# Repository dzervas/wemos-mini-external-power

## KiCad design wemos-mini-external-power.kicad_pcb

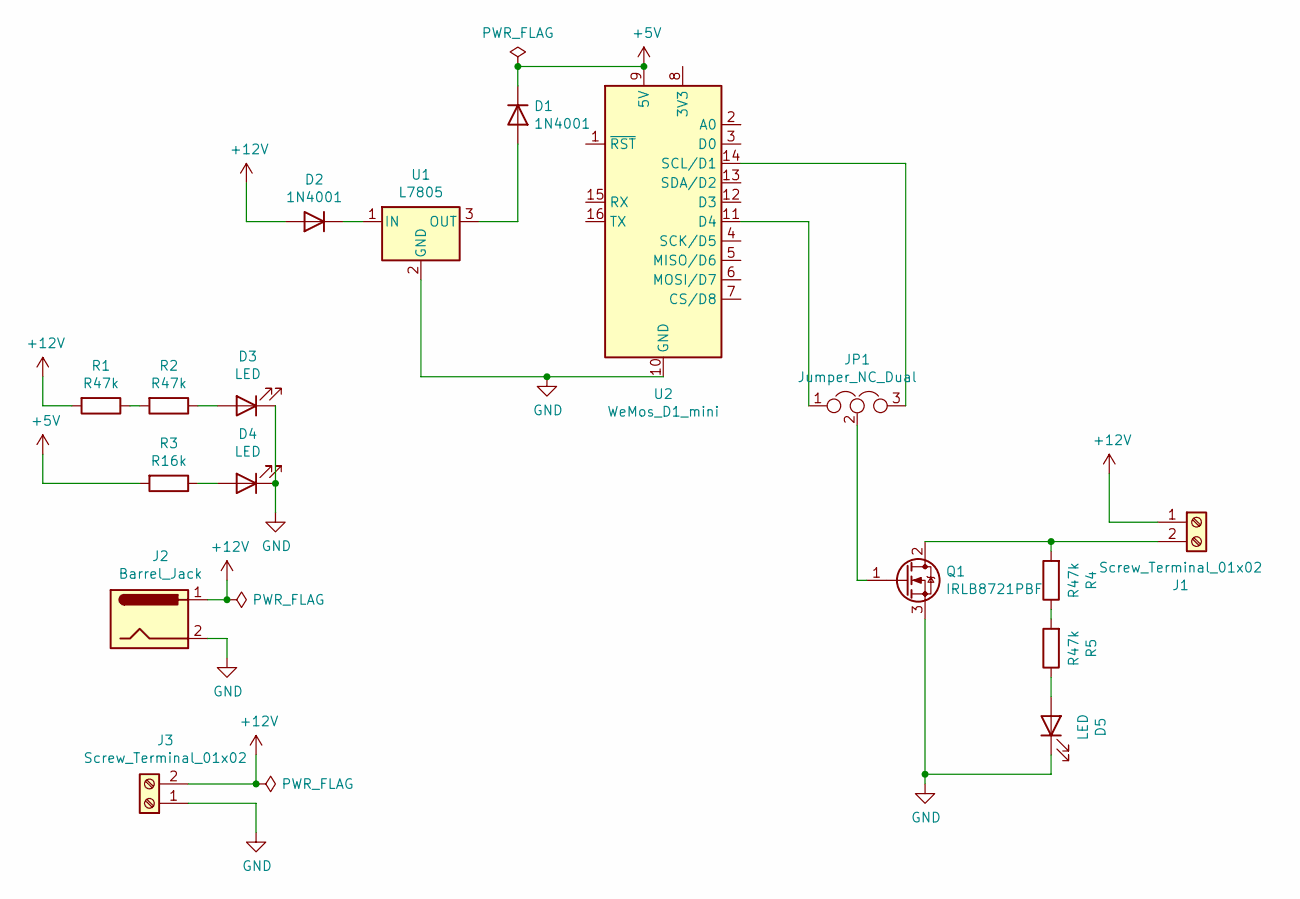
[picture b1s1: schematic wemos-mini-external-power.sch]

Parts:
D1, D2: 1N4001; D_DO-41_SOD81_P7.62mm_Horizontal
D3, D4, D5: LED; LED_1206_3216Metric
J1, J3: Screw_Terminal_01x02; TerminalBlock_4Ucon_1x02_P3.50mm_Horizontal
J2: Barrel_Jack; BarrelJack_CUI_PJ-102AH_Horizontal
JP1: Jumper_NC_Dual; PinHeader_1x03_P2.54mm_Vertical
Q1: IRLB8721PBF; TO-220-3_Vertical
R1, R2, R4, R5: R47k; R_0805_2012Metric
R3: R16k; R_0805_2012Metric
U1: L7805; TO-220-3_Horizontal_TabDown
U2: WeMos_D1_mini; WEMOS_D1_mini_light

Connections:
+5V: D1.1 (K), R3.2, U2.9 (5V)
+12V: D2.2 (A), J1.1, J2.1, J3.2, R1.2
GND: D3.1 (K), D4.1 (K), D5.1 (K), J2.2, J3.1, Q1.3 (S), U1.2 (GND), U2.10 (GND)
unnamed: D1.2 (A), U1.3 (OUT)
unnamed: D2.1 (K), U1.1 (IN)
unnamed: D3.2 (A), R2.1
unnamed: D4.2 (A), R3.1
unnamed: D5.2 (A), R5.1
unnamed: J1.2, Q1.2 (D), R4.2
unnamed: JP1.1, U2.11 (D4)
unnamed: JP1.2, Q1.1 (G)
unnamed: JP1.3, U2.14 (SCL/D1)
unnamed: R1.1, R2.2
unnamed: R4.1, R5.2

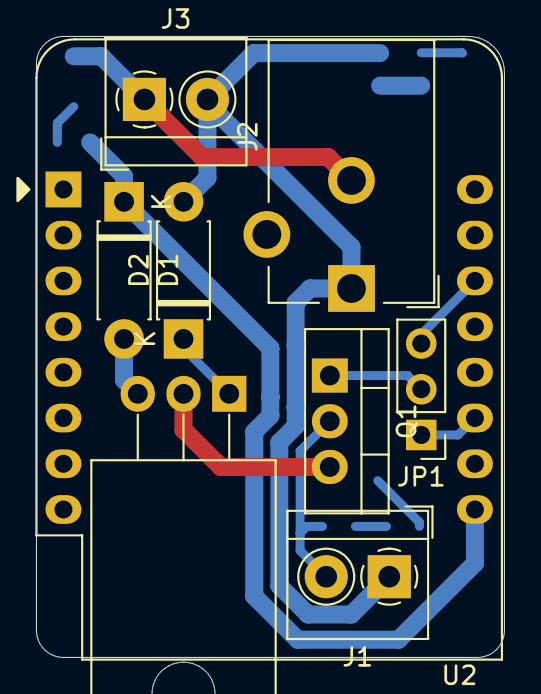
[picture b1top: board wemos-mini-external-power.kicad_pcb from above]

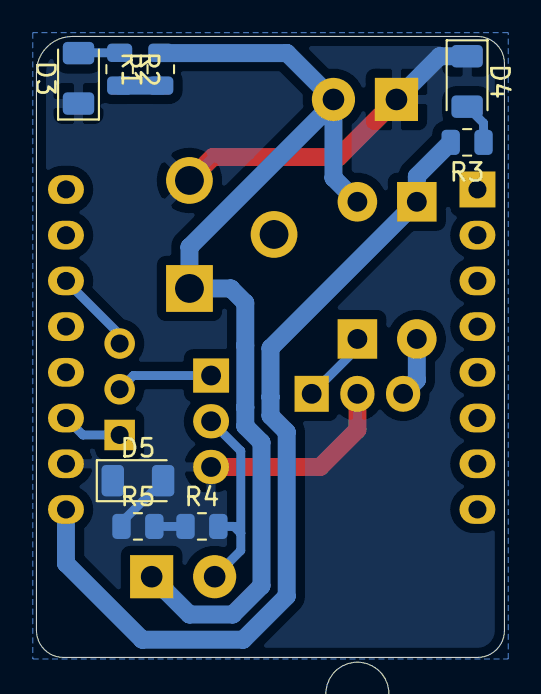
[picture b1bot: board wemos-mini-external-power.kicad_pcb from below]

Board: 2 copper layers, 26.0 x 34.5 mm, 17 parts (8 on the bottom side), 14 nets.

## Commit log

2020-11-06 Add first dummy version
2020-12-13 Update gitignore
2020-12-16 Move traces to the back
2020-12-29 Ignore svgs
2023-06-18 No idea
